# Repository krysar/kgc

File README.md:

# Kerbal Guidance Computer

A HW flight computer for Kerbal Space Program inspired by NASA's DSKY - interface for [Apollo Guidance Computer](https://en.wikipedia.org/wiki/Apollo_Guidance_Computer).

It consists of Python script for PC which grab data from the [kRPC mod](https://krpc.github.io/krpc/index.html), KGC's DSKY based on Raspberry Pi Pico and program for it. DSKY communicate with PC via UART, so you also need some USB-UART converter. KiCad project for DSKY is located in kicad directory.

**Project is still in developement, it's pretty buggy and some of planned features are stil unimplemented.**

## Features
### Implemented
- Display several flight informations depending on selected Verb and Noun.
- Ship control:
    - SAS control
    - RCS control
    - Gear control
    - Lights control
    - Brakes control
    - Solar panels control (extend/retract)
    - Antennas control (extend/retract)
    - Next stage activation
    - Abort group activation
- Maneuver planning
- MechJeb control:
    - Ascent guidance
### Planned
- Ship control:
    - Thrust control
- MechJeb control:
    - Landing guidance
    - Rendezvous autopilot
    - Docking autopilot
    - Maneuver planner

## Installation
TODO

## Usage
TODO

## Verbs and Nouns list

| Verb | Noun | Input/Output                                 | Actions                               | Notes                                                                |
|------|------|----------------------------------------------|---------------------------------------|----------------------------------------------------------------------|
| 00   | 00   |                                              | No op                                 |                                                                      |
| 01   | 01   |                                              | Disconnect from server                |                                                                      |
| 00   | 02   |                                              | Reboot                                |                                                                      |
| 01   | 00   |                                              | No op                                 |                                                                      |
| 01   | 01   | O: Altitude above sea level [m]              |                                       |                                                                      |
|      |      | O: Apoapsis [m]                              |                                       |                                                                      |
|      |      | O: Periapsis [m]                             |                                       |                                                                      |
| 01   | 02   | O: Orbital inclination [°]                   |                                       |                                                                      |
|      |      | O: Orbital eccentricity [°]                  |                                       |                                                                      |
|      |      | O: Mean anomaly [°]                          |                                       |                                                                      |
| 01   | 03   | O: Time to apoapsis [hrs]                    |                                       |                                                                      |
|      |      | O: Time to apoapsis [min]                    |                                       |                                                                      |
|      |      | O: Time to apoapsis [sec]                    |                                       |                                                                      |
| 01   | 04   | O: Time to apoapsis [days]                   |                                       |                                                                      |
|      |      | O: Time to apoapsis [hrs]                    |                                       |                                                                      |
|      |      | O: Time to apoapsis [min]                    |                                       | Kerbin days                                                          |
| 01   | 05   | O: Time to periapsis [hrs]                   |                                       |                                                                      |
|      |      | O: Time to periapsis [min]                   |                                       |                                                                      |
|      |      | O: Time to periapsis [sec]                   |                                       |                                                                      |
| 01   | 06   | O: Time to periapsis [days]                  |                                       |                                                                      |
|      |      | O: Time to periapsis [hrs]                   |                                       |                                                                      |
|      |      | O: Time to periapsis [min]                   |                                       | Kerbin days                                                          |
| 01   | 07   | O: Orbital period [hrs]                      |                                       |                                                                      |
|      |      | O: Orbital period [min]                      |                                       |                                                                      |
|      |      | O: Orbital period [sec]                      |                                       |                                                                      |
| 01   | 08   | O: Orbital period [days]                     |                                       |                                                                      |
|      |      | O: Orbital period [hrs]                      |                                       |                                                                      |
|      |      | O: Orbital period [min]                      |                                       | Kerbin days                                                          |
| 01   | 09   | O: Time to sphere of influence change [hrs]  |                                       |                                                                      |
|      |      | O: Time to sphere of influence change [min]  |                                       |                                                                      |
|      |      | O: Time to sphere of influence change [sec]  |                                       |                                                                      |
| 01   | 10   | O: Time to sphere of influence change [days] |                                       |                                                                      |
|      |      | O: Time to sphere of influence change [hrs]  |                                       |                                                                      |
|      |      | O: Time to sphere of influence change [min]  |                                       | Kerbin days                                                          |
| 01   | 11   | O: Heading [°]                               |                                       | TODO: check ref. frame                                               |
|      |      | O: Pitch [°]                                 |                                       | TODO: check ref. frame                                               |
|      |      | O: Roll [°]                                  |                                       | TODO: check ref. frame                                               |
| 01   | 12   | O: Velocity - x [m/s]                        |                                       | TODO: check ref. frame                                               |
|      |      | O: Velocity - y [m/s]                        |                                       |                                                                      |
|      |      | O: Velocity - z [m/s]                        |                                       |                                                                      |
| 01   | 13   | O: Orbital speed [m/s]                       |                                       |                                                                      |
|      |      | O: Surface speed [m/s]                       |                                       |                                                                      |
| 02   | 00   |                                              | No op                                 |                                                                      |
| 02   | 01   | O: Mission elapsed time [hrs]                |                                       |                                                                      |
|      |      | O: Mission elapsed time [min]                |                                       |                                                                      |
|      |      | O: Mission elapsed time [sec]                |                                       | Strange bug                                                          |
| 02   | 02   | O: Mission elapsed time [days]               |                                       |                                                                      |
|      |      | O: Mission elapsed time [min]                |                                       | Strange bug                                                          |
|      |      | O: Mission elapsed time [hrs]                |                                       | Strange bug                                                          |
| 02   | 03   | O: Mass [kg]                                 |                                       |                                                                      |
|      |      | O: Available thurst [N]                      |                                       |                                                                      |
|      |      | O: Specific impulse [sec]                    |                                       |                                                                      |
| 02   | 04   | O: Electric charge capacity [-]              |                                       |                                                                      |
|      |      | O: Monopropellant capacity [-]               |                                       |                                                                      |
|      |      | O: Liquid fuel capacity [-]                  |                                       |                                                                      |
| 02   | 05   | O: Electric charge amount [-]                |                                       | TODO: float                                                          |
|      |      | O: Monopropellant amount [-]                 |                                       | TODO: float                                                          |
|      |      | O: Liquid fuel amount [-]                    |                                       | TODO: float                                                          |
| 02   | 06   | O: Electric charge amount [%]                |                                       |                                                                      |
|      |      | O: Monopropellant amount [%]                 |                                       |                                                                      |
|      |      | O: Liquid fuel amount [%]                    |                                       |                                                                      |
| 02   | 07   | O: Electric charge capacity [-]              |                                       |                                                                      |
|      |      | O: Electric charge amount [-]                |                                       | TODO: float                                                          |
|      |      | O: Electric charge amount [%]                |                                       |                                                                      |
| 02   | 08   | O: Monopropellant capacity [-]               |                                       |                                                                      |
|      |      | O: Monopropellant amount [-]                 |                                       | TODO: float                                                          |
|      |      | O: Monopropellant amount [%]                 |                                       |                                                                      |
| 02   | 09   | O: Liquid fuel capacity [-]                  |                                       |                                                                      |
|      |      | O: Liquid fuel amount [-]                    |                                       | TODO: float                                                          |
|      |      | O: Liquid fuel amount [%]                    |                                       |                                                                      |
| 03   | 01   | O: Surface speed [m/s]                       |                                       |                                                                      |
|      |      | O: Vertical speed [m/s]                      |                                       |                                                                      |
|      |      | O: Altitude above surface [m]                |                                       |                                                                      |
| 03   | 02   | O: Altitude above sea level                  |                                       |                                                                      |
|      |      | O: Apoapsis [m]                              |                                       |                                                                      |
|      |      | O: Orbital inclination [°]                   |                                       |                                                                      |
| 03   | 03   | O: Apoapsis [m]                              |                                       |                                                                      |
|      |      | O: Periapsis [m]                             |                                       |                                                                      |
|      |      | O: Orbital inclination [°]                   |                                       |                                                                      |
| 04   | 01   | O: Time to node [hrs]                        |                                       |                                                                      |
|      |      | O: Time to node [min]                        |                                       |                                                                      |
|      |      | O: Time to node [sec]                        |                                       |                                                                      |
| 04   | 02   | O: Δv magnitude - prograde direction [m/s]   |                                       |                                                                      |
|      |      | O: Δv magnitude - normal direction [m/s]     |                                       |                                                                      |
|      |      | O: Δv magnitude - radial direction [m/s]     |                                       |                                                                      |
| 04   | 03   | O: Δv [m/s]                                  |                                       |                                                                      |
|      |      | O: Remaining Δv [m/s]                        |                                       |                                                                      |
|      |      | O: Time to node [sec]                        |                                       |                                                                      |
| 04   | 04   | O: Result apoapsis [m]                       |                                       |                                                                      |
|      |      | O: Result periapsis [m]                      |                                       |                                                                      |
|      |      | O: Result inclination [°]                    |                                       |                                                                      |
| 05   | 01   | O: Altitude above surface [m]                |                                       |                                                                      |
|      |      | O: Surface speed [m/s]                       |                                       |                                                                      |
|      |      | O: Liquid fuel amount [%]                    |                                       |                                                                      |
| 05   | 02   | O: Altitude above surface [m]                |                                       |                                                                      |
|      |      | O: Vertical speed [m/s]                      |                                       |                                                                      |
|      |      | O: Horizontal speed [m/s]                    |                                       |                                                                      |
| 12   | 01   |                                              | Activate SAS in stability assist mode | Then return to previous Verb + Noun                                  |
| 12   | 02   |                                              | Activate SAS in maneuver mode         | Then return to previous Verb + Noun                                  |
| 12   | 03   |                                              | Activate SAS in prograde mode         | Then return to previous Verb + Noun                                  |
| 12   | 04   |                                              | Activate SAS in retrograde mode       | Then return to previous Verb + Noun                                  |
| 12   | 05   |                                              | Activate SAS in normal mode           | Then return to previous Verb + Noun                                  |
| 12   | 06   |                                              | Activate SAS in anti-normal mode      | Then return to previous Verb + Noun                                  |
| 12   | 07   |                                              | Activate SAS in radial mode           | Then return to previous Verb + Noun                                  |
| 12   | 08   |                                              | Activate SAS in anti-radial mode      | Then return to previous Verb + Noun                                  |
| 12   | 09   |                                              | Activate SAS in target mode           | Then return to previous Verb + Noun                                  |
| 12   | 10   |                                              | Activate SAS in anti-targer mode      | Then return to previous Verb + Noun                                  |
| 12   | 11   |                                              | Deactivate SAS                        | Then return to previous Verb + Noun                                  |
| 12   | 12   |                                              | Activate RCS                          | Then return to previous Verb + Noun                                  |
| 12   | 13   |                                              | Deactivate RCS                        | Then return to previous Verb + Noun                                  |
| 12   | 14   |                                              | Extend gear                           | Then return to previous Verb + Noun                                  |
| 12   | 15   |                                              | Retract gear                          | Then return to previous Verb + Noun                                  |
| 12   | 16   |                                              | Activate ligts                        | Then return to previous Verb + Noun                                  |
| 12   | 17   |                                              | Deactivate lights                     | Then return to previous Verb + Noun                                  |
| 12   | 18   |                                              | Activate brakes                       | Then return to previous Verb + Noun                                  |
| 12   | 19   |                                              | Deactivate brakes                     | Then return to previous Verb + Noun                                  |
| 12   | 20   |                                              | Extend solar panels                   | Then return to previous Verb + Noun                                  |
| 12   | 21   |                                              | Retract solar panels                  | Then return to previous Verb + Noun                                  |
| 12   | 22   |                                              | Extend antennas                       | Then return to previous Verb + Noun                                  |
| 12   | 23   |                                              | Retract antennas                      | Then return to previous Verb + Noun                                  |
| 12   | 24   |                                              | Activate next stage                   | Then return to previous Verb + Noun                                  |
| 12   | 25   |                                              | Activate abort group                  | Then return to previous Verb + Noun                                  |
| 12   | 30   |                                              | Initialize node creation              |                                                                      |
| 12   | 31   | I: UT - year                                 |                                       |                                                                      |
|      |      | I: UT - day                                  |                                       |                                                                      |
| 12   | 32   | O: UT - year                                 |                                       |                                                                      |
|      |      | O: UT - day                                  |                                       |                                                                      |
| 12   | 33   | I: UT - hour                                 |                                       |                                                                      |
|      |      | I: UT - minute                               |                                       |                                                                      |
|      |      | I: UT - second                               |                                       |                                                                      |
| 12   | 34   | O: UT - hour                                 |                                       |                                                                      |
|      |      | O: UT - minute                               |                                       |                                                                      |
|      |      | O: UT - second                               |                                       |                                                                      |
| 12   | 35   | I: Δv - prograde [m/s]                       |                                       |                                                                      |
|      |      | I: Δv - normal [m/s]                         |                                       |                                                                      |
|      |      | I: Δv - radial [m/s]                         |                                       |                                                                      |
| 12   | 36   | O: Δv - prograde [m/s]                       |                                       |                                                                      |
|      |      | O: Δv - normal [m/s]                         |                                       |                                                                      |
|      |      | O: Δv - radial [m/s]                         |                                       |                                                                      |
| 12   | 37   |                                              | Create node                           | Incorrect time                                                       |
| 13   | 00   |                                              | Initialize ascent autpoilot           | MechJeb is used                                                      |
| 13   | 01   | I: Orbit altitude [km]                       |                                       |                                                                      |
|      |      | I: Orbit inclination [°]                     |                                       |                                                                      |
|      |      | I: Ascent profile {1; 2; 3}                  |                                       | 1 = Classic ascent profile                                           |
|      |      |                                              |                                       | 2 = Stock-style GravityTurn ascent profile                           |
|      |      |                                              |                                       | 3 = Primer Vector Guidance ascent profile                            |
| 13   | 02   | O: Orbit altitude [km]                       |                                       |                                                                      |
|      |      | O: Orbit inclination [°]                     |                                       |                                                                      |
|      |      | O: Ascent profile {1; 2; 3}                  |                                       |                                                                      |
| 13   | 03   | I: Acceleration limit [m/s]                  |                                       | -1 for disable; -2 for ignore                                        |
|      |      | I: Throttle limit [%]                        |                                       | -1 for disable; -2 for ignore                                        |
| 13   | 04   | O: Acceleration limit [m/s]                  |                                       |                                                                      |
|      |      | O: Throttle limit [%]                        |                                       |                                                                      |
| 13   | 05   | I: Force roll - climb [°]                    |                                       | -1 for disable; -2 for ignore (whole force roll)                     |
|      |      | I: Force roll - turn [°]                     |                                       |                                                                      |
| 13   | 06   | O: Force roll - climb [°]                    |                                       |                                                                      |
|      |      | O: Force roll - turn [°]                     |                                       |                                                                      |
| 13   | 07   | I: Autostage pre-delay [s]                   |                                       | -1 for disable; -2 for ignore (whole autostage)                      |
|      |      | I: Autostage post-delay [s]                  |                                       |                                                                      |
|      |      | I: Clamp autostage thrust [%]                |                                       |                                                                      |
| 13   | 08   | O: Autostage pre-delay [s]                   |                                       |                                                                      |
|      |      | O: Autostage post-delay [s]                  |                                       |                                                                      |
|      |      | O: Clamp autostage thrust [%]                |                                       |                                                                      |
| 13   | 09   | I: Minimal throttle [%]                      |                                       | -1 for disable; -2 for ignore                                        |
|      |      | I: Autostage stop stage                      |                                       | Details in truth table                                               |
|      |      | I: Other options                             |                                       |                                                                      |
| 13   | 10   | O: Minimal throttle [%]                      |                                       |                                                                      |
|      |      | O: Autostage stop stage                      |                                       |                                                                      |
|      |      | O: Other options                             |                                       |                                                                      |
| 13   | 11   | I: Turn start altitude [km]                  |                                       | Classic ascent profile                                               |
|      |      | I: Turn start velocity [m/s]                 |                                       | Classic ascent profile                                               |
|      |      | I: Turn end altitude [km]                    |                                       | Classic ascent profile                                               |
| 13   | 12   | O: Turn start altitude [km]                  |                                       | Classic ascent profile                                               |
|      |      | O: Turn start velocity [m/s]                 |                                       | Classic ascent profile                                               |
|      |      | O: Turn end altitude [km]                    |                                       | Classic ascent profile                                               |
| 13   | 13   | I: Final flight path angle [°]               |                                       | Classic ascent profile; -1 for disable; -2 for ignore                |
|      |      | I: Turn shape [%]                            |                                       | Classic ascent profile; -1 for disable; -2 for ignore                |
| 13   | 14   | O: Final flight path angle [°]               |                                       | Classic ascent profile                                               |
|      |      | O: Turn shape [%]                            |                                       | Classic ascent profile                                               |
| 13   | 15   | I: Turn start altitude [km]                  |                                       | Stock-style GravityTurn ascent profile                               |
|      |      | I: Turn start velocity [m/s]                 |                                       | Stock-style GravityTurn ascent profile                               |
|      |      | I: Turn start pitch [°]                      |                                       | Stock-style GravityTurn ascent profile                               |
| 13   | 16   | O: Turn start altitude [km]                  |                                       | Stock-style GravityTurn ascent profile                               |
|      |      | O: Turn start velocity [m/s]                 |                                       | Stock-style GravityTurn ascent profile                               |
|      |      | O: Turn start pitch [°]                      |                                       | Stock-style GravityTurn ascent profile                               |
| 13   | 17   | I: Intermediate altitude [km]                |                                       | Stock-style GravityTurn ascent profile                               |
|      |      | I: Hold AP time [s]                          |                                       | Stock-style GravityTurn ascent profile                               |
| 13   | 18   | O: Intermediate altitude [km]                |                                       | Stock-style GravityTurn ascent profile                               |
|      |      | O: Hold AP time [s]                          |                                       | Stock-style GravityTurn ascent profile                               |
| 13   | 19   | I: Apoapsis altitude [km]                    |                                       | Primer Vector Guidance ascent profile                                |
|      |      | I: Attach altitude [km]                      |                                       | Primer Vector Guidance ascent profile                                |
|      |      | I: Booster pitch start velocity [m/s]        |                                       | Primer Vector Guidance ascent profile                                |
| 13   | 20   | O: Apoapsis altitude [km]                    |                                       | Primer Vector Guidance ascent profile                                |
|      |      | O: Attach altitude [km]                      |                                       | Primer Vector Guidance ascent profile                                |
|      |      | O: Booster pitch start velocity [m/s]        |                                       | Primer Vector Guidance ascent profile                                |
| 13   | 21   | I: Booster pitch rate [°/s]                  |                                       | Primer Vector Guidance ascent profile                                |
|      |      | I: PVG after stage                           |                                       | Primer Vector Guidance ascent profile; -1 for disable; -2 for ignore |
| 13   | 22   | O: Booster pitch rate [°/s]                  |                                       | Primer Vector Guidance ascent profile                                |
|      |      | O: PVG after stage                           |                                       | Primer Vector Guidance ascent profile                                |
| 13   | 23   | I: Q trigger [kPa]                           |                                       | Primer Vector Guidance ascent profile                                |
|      |      | I: Fixed coast length [s]                    |                                       | Primer Vector Guidance ascent profile; -1 for disable; -2 for ignore |
| 13   | 24   | O: Q trigger [kPa]                           |                                       | Primer Vector Guidance ascent profile                                |
|      |      | O: Fixed coast length [s]                    |                                       | Primer Vector Guidance ascent profile                                |
| 13   | 25   |                                              | Enage ascent autopilot                |                                                                      |
| 13   | 26   |                                              | Disenage ascent autopilot             |                                                                      |

## Truth table for other options value in Ascent autopilot

| Prevent overheat | Solar panels | Antennas | Skip circularization | Dec |
|------------------|--------------|----------|----------------------|-----|
| 0                | 0            | 0        | 0                    | 0   |
| 0                | 0            | 0        | 1                    | 1   |
| 0                | 0            | 1        | 0                    | 2   |
| 0                | 0            | 1        | 1                    | 3   |
| 0                | 1            | 0        | 0                    | 4   |
| 0                | 1            | 0        | 1                    | 5   |
| 0                | 1            | 1        | 0                    | 6   |
| 0                | 1            | 1        | 1                    | 7   |
| 1                | 0            | 0        | 0                    | 8   |
| 1                | 0            | 0        | 1                    | 9   |
| 1                | 0            | 1        | 0                    | 10  |
| 1                | 0            | 1        | 1                    | 11  |
| 1                | 1            | 0        | 0                    | 12  |
| 1                | 1            | 0        | 1                    | 13  |
| 1                | 1            | 1        | 0                    | 14  |
| 1                | 1            | 1        | 1                    | 15  |

## Error codes
### Ascent guidance:
- 1301: Noun doesn't exist
- 1302: Autopilot wasn't initialized
- 1303: Ascent profile selected in V13;N01 doesn't exist

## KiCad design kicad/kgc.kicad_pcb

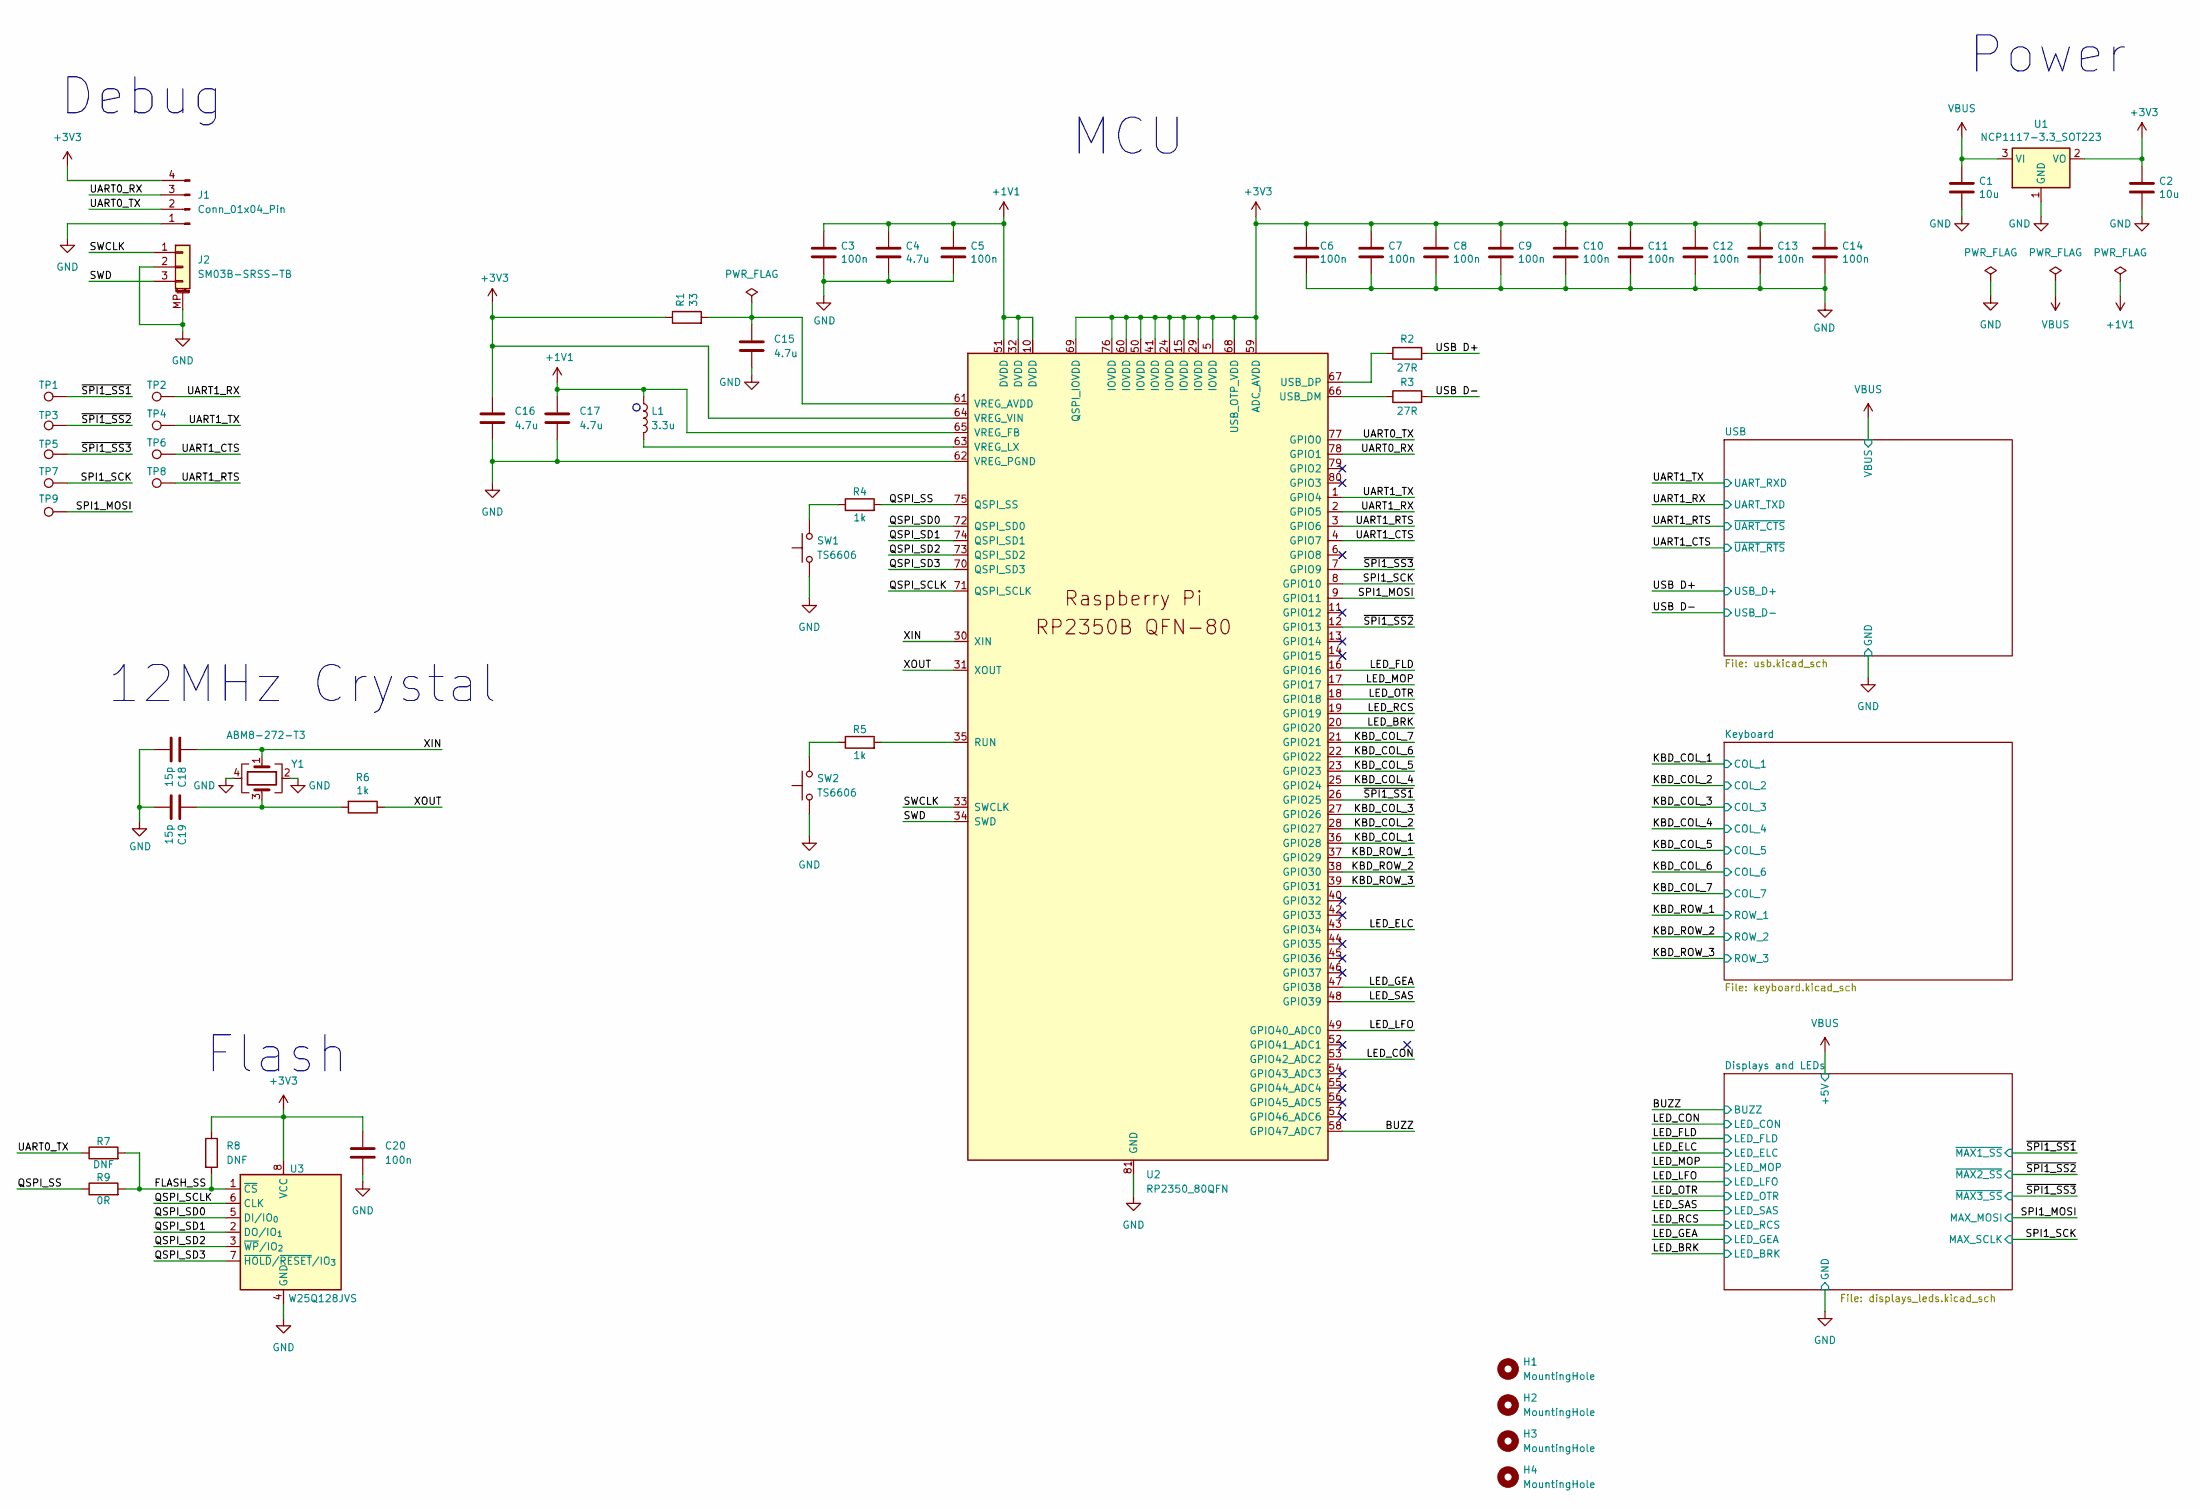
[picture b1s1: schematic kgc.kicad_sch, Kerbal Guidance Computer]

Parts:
C1, C2: 10u; C_0603_1608Metric_Pad1.08x0.95mm_HandSolder
C3, C5, C6, C7, C8, C9, C10, C11, C12, C13, C14, C20: 100n; C_0603_1608Metric_Pad1.08x0.95mm_HandSolder
C4, C15, C16, C17: 4.7u; C_0603_1608Metric_Pad1.08x0.95mm_HandSolder
C18, C19: 15p; C_0603_1608Metric_Pad1.08x0.95mm_HandSolder
H1, H2, H3, H4: MountingHole; MountingHole_3.2mm_M3
J1: Conn_01x04_Pin; PinHeader_1x04_P2.54mm_Horizontal
J2: SM03B-SRSS-TB; JST_SH_SM03B-SRSS-TB_1x03-1MP_P1.00mm_Horizontal
L1: 3.3u; L_pol_2016
R1: 33; R_0603_1608Metric_Pad0.98x0.95mm_HandSolder
R2, R3: 27R; R_0603_1608Metric_Pad0.98x0.95mm_HandSolder
R4, R5, R6: 1k; R_0603_1608Metric_Pad0.98x0.95mm_HandSolder
R7, R8: DNF; R_0603_1608Metric_Pad0.98x0.95mm_HandSolder
R9: 0R; R_0603_1608Metric_Pad0.98x0.95mm_HandSolder
SW1, SW2: TS6606; SW_Tactile_SKHH_Angled
TP1, TP2, TP3, TP4, TP5, TP6, TP7, TP8, TP9: TestPoint; TestPoint_Plated_Hole_D2.0mm
U1: NCP1117-3.3_SOT223; SOT-223-3_TabPin2; LCSC C26537
U2: RP2350_80QFN; RP2350-QFN-80-1EP_10x10_P0.4mm_EP3.4x3.4mm_ThermalVias; LCSC C42415655
U3: W25Q128JVS; SOIC-8_5.3x5.3mm_P1.27mm; LCSC C97521
Y1: ABM8-272-T3; Crystal_SMD_3225-4Pin_3.2x2.5mm; LCSC C20625731

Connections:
+1V1: C3.1, C4.1, C5.1, C17.1, L1.1, U2.10 (DVDD), U2.32 (DVDD), U2.51 (DVDD), U2.65 (VREG_FB)
+3V3: C2.1, C6.1, C7.1, C8.1, C9.1, C10.1, C11.1, C12.1, C13.1, C14.1, C16.1, C20.1, J1.4, R1.1, R8.1, U1.2 (VO), U2.5 (IOVDD), U2.15 (IOVDD), U2.24 (IOVDD), U2.29 (IOVDD), U2.41 (IOVDD), U2.50 (IOVDD), U2.59 (ADC_AVDD), U2.60 (IOVDD), U2.64 (VREG_VIN), U2.68 (USB_OTP_VDD), U2.69 (QSPI_IOVDD), U2.76 (IOVDD), U3.8 (VCC)
/BUZZ: U2.58 (GPIO47_ADC7); also elsewhere on the board
/FLASH_SS: R7.2, R8.2, R9.2, U3.1 (~CS)
/KBD_COL_1: U2.36 (GPIO28); also elsewhere on the board
/KBD_COL_2: U2.28 (GPIO27); also elsewhere on the board
/KBD_COL_3: U2.27 (GPIO26); also elsewhere on the board
/KBD_COL_4: U2.25 (GPIO24); also elsewhere on the board
/KBD_COL_5: U2.23 (GPIO23); also elsewhere on the board
/KBD_COL_6: U2.22 (GPIO22); also elsewhere on the board
/KBD_COL_7: U2.21 (GPIO21); also elsewhere on the board
/KBD_ROW_1: U2.37 (GPIO29); also elsewhere on the board
/KBD_ROW_2: U2.38 (GPIO30); also elsewhere on the board
/KBD_ROW_3: U2.39 (GPIO31); also elsewhere on the board
/LED_BRK: U2.20 (GPIO20); also elsewhere on the board
/LED_CON: U2.53 (GPIO42_ADC2); also elsewhere on the board
/LED_ELC: U2.43 (GPIO34); also elsewhere on the board
/LED_FLD: U2.16 (GPIO16); also elsewhere on the board
/LED_GEA: U2.47 (GPIO38); also elsewhere on the board
/LED_LFO: U2.49 (GPIO40_ADC0); also elsewhere on the board
/LED_MOP: U2.17 (GPIO17); also elsewhere on the board
/LED_OTR: U2.18 (GPIO18); also elsewhere on the board
/LED_RCS: U2.19 (GPIO19); also elsewhere on the board
/LED_SAS: U2.48 (GPIO39); also elsewhere on the board
/QSPI_SCLK: U2.71 (QSPI_SCLK), U3.6 (CLK)
/QSPI_SD0: U2.72 (QSPI_SD0), U3.5 (DI/IO_{0})
/QSPI_SD1: U2.74 (QSPI_SD1), U3.2 (DO/IO_{1})
/QSPI_SD2: U2.73 (QSPI_SD2), U3.3 (~WP/IO_{2})
/QSPI_SD3: U2.70 (QSPI_SD3), U3.7 (~HOLD/~RESET/IO_{3})
/QSPI_SS: R4.2, R9.1, U2.75 (QSPI_SS)
/SPI1_MOSI: TP9.1, U2.9 (GPIO11); also elsewhere on the board
/SPI1_SCK: TP7.1, U2.8 (GPIO10); also elsewhere on the board
/SWCLK: J2.1, U2.33 (SWCLK)
/SWD: J2.3, U2.34 (SWD)
/UART0_RX: J1.3, U2.78 (GPIO1)
/UART0_TX: J1.2, R7.1, U2.77 (GPIO0)
/UART1_CTS: TP6.1, U2.4 (GPIO7); also elsewhere on the board
/UART1_RTS: TP8.1, U2.3 (GPIO6); also elsewhere on the board
/UART1_RX: TP2.1, U2.2 (GPIO5); also elsewhere on the board
/UART1_TX: TP4.1, U2.1 (GPIO4); also elsewhere on the board
/USB D+: R2.2; also elsewhere on the board
/USB D-: R3.2; also elsewhere on the board
/XIN: C18.1, U2.30 (XIN), Y1.1
/XOUT: R6.1, U2.31 (XOUT)
/~SPI1_SS1: TP1.1, U2.26 (GPIO25); also elsewhere on the board
/~SPI1_SS2: TP3.1, U2.12 (GPIO13); also elsewhere on the board
/~SPI1_SS3: TP5.1, U2.7 (GPIO9); also elsewhere on the board
GND: C1.2, C2.2, C3.2, C4.2, C5.2, C6.2, C7.2, C8.2, C9.2, C10.2, C11.2, C12.2, C13.2, C14.2, C15.2, C16.2, C17.2, C18.2, C19.2, C20.2, J1.1, J2.2, J2.MP (MountPin), SW1.1, SW2.1, U1.1 (GND), U2.62 (VREG_PGND), U2.81 (GND), U3.4 (GND), Y1.2, Y1.4; also elsewhere on the board
unnamed: C19.1, R6.2, Y1.3
unnamed: R4.1, SW1.2
unnamed: R5.1, SW2.2
unnamed: R5.2, U2.35 (RUN)
unnamed: R3.1, U2.66 (USB_DM)
unnamed: R2.1, U2.67 (USB_DP)
unnamed: C15.1, R1.2, U2.61 (VREG_AVDD)
unnamed: L1.2, U2.63 (VREG_LX)
VBUS: C1.1, U1.3 (VI); also elsewhere on the board

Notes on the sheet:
Debug
12MHz Crystal
Flash
MCU
Power

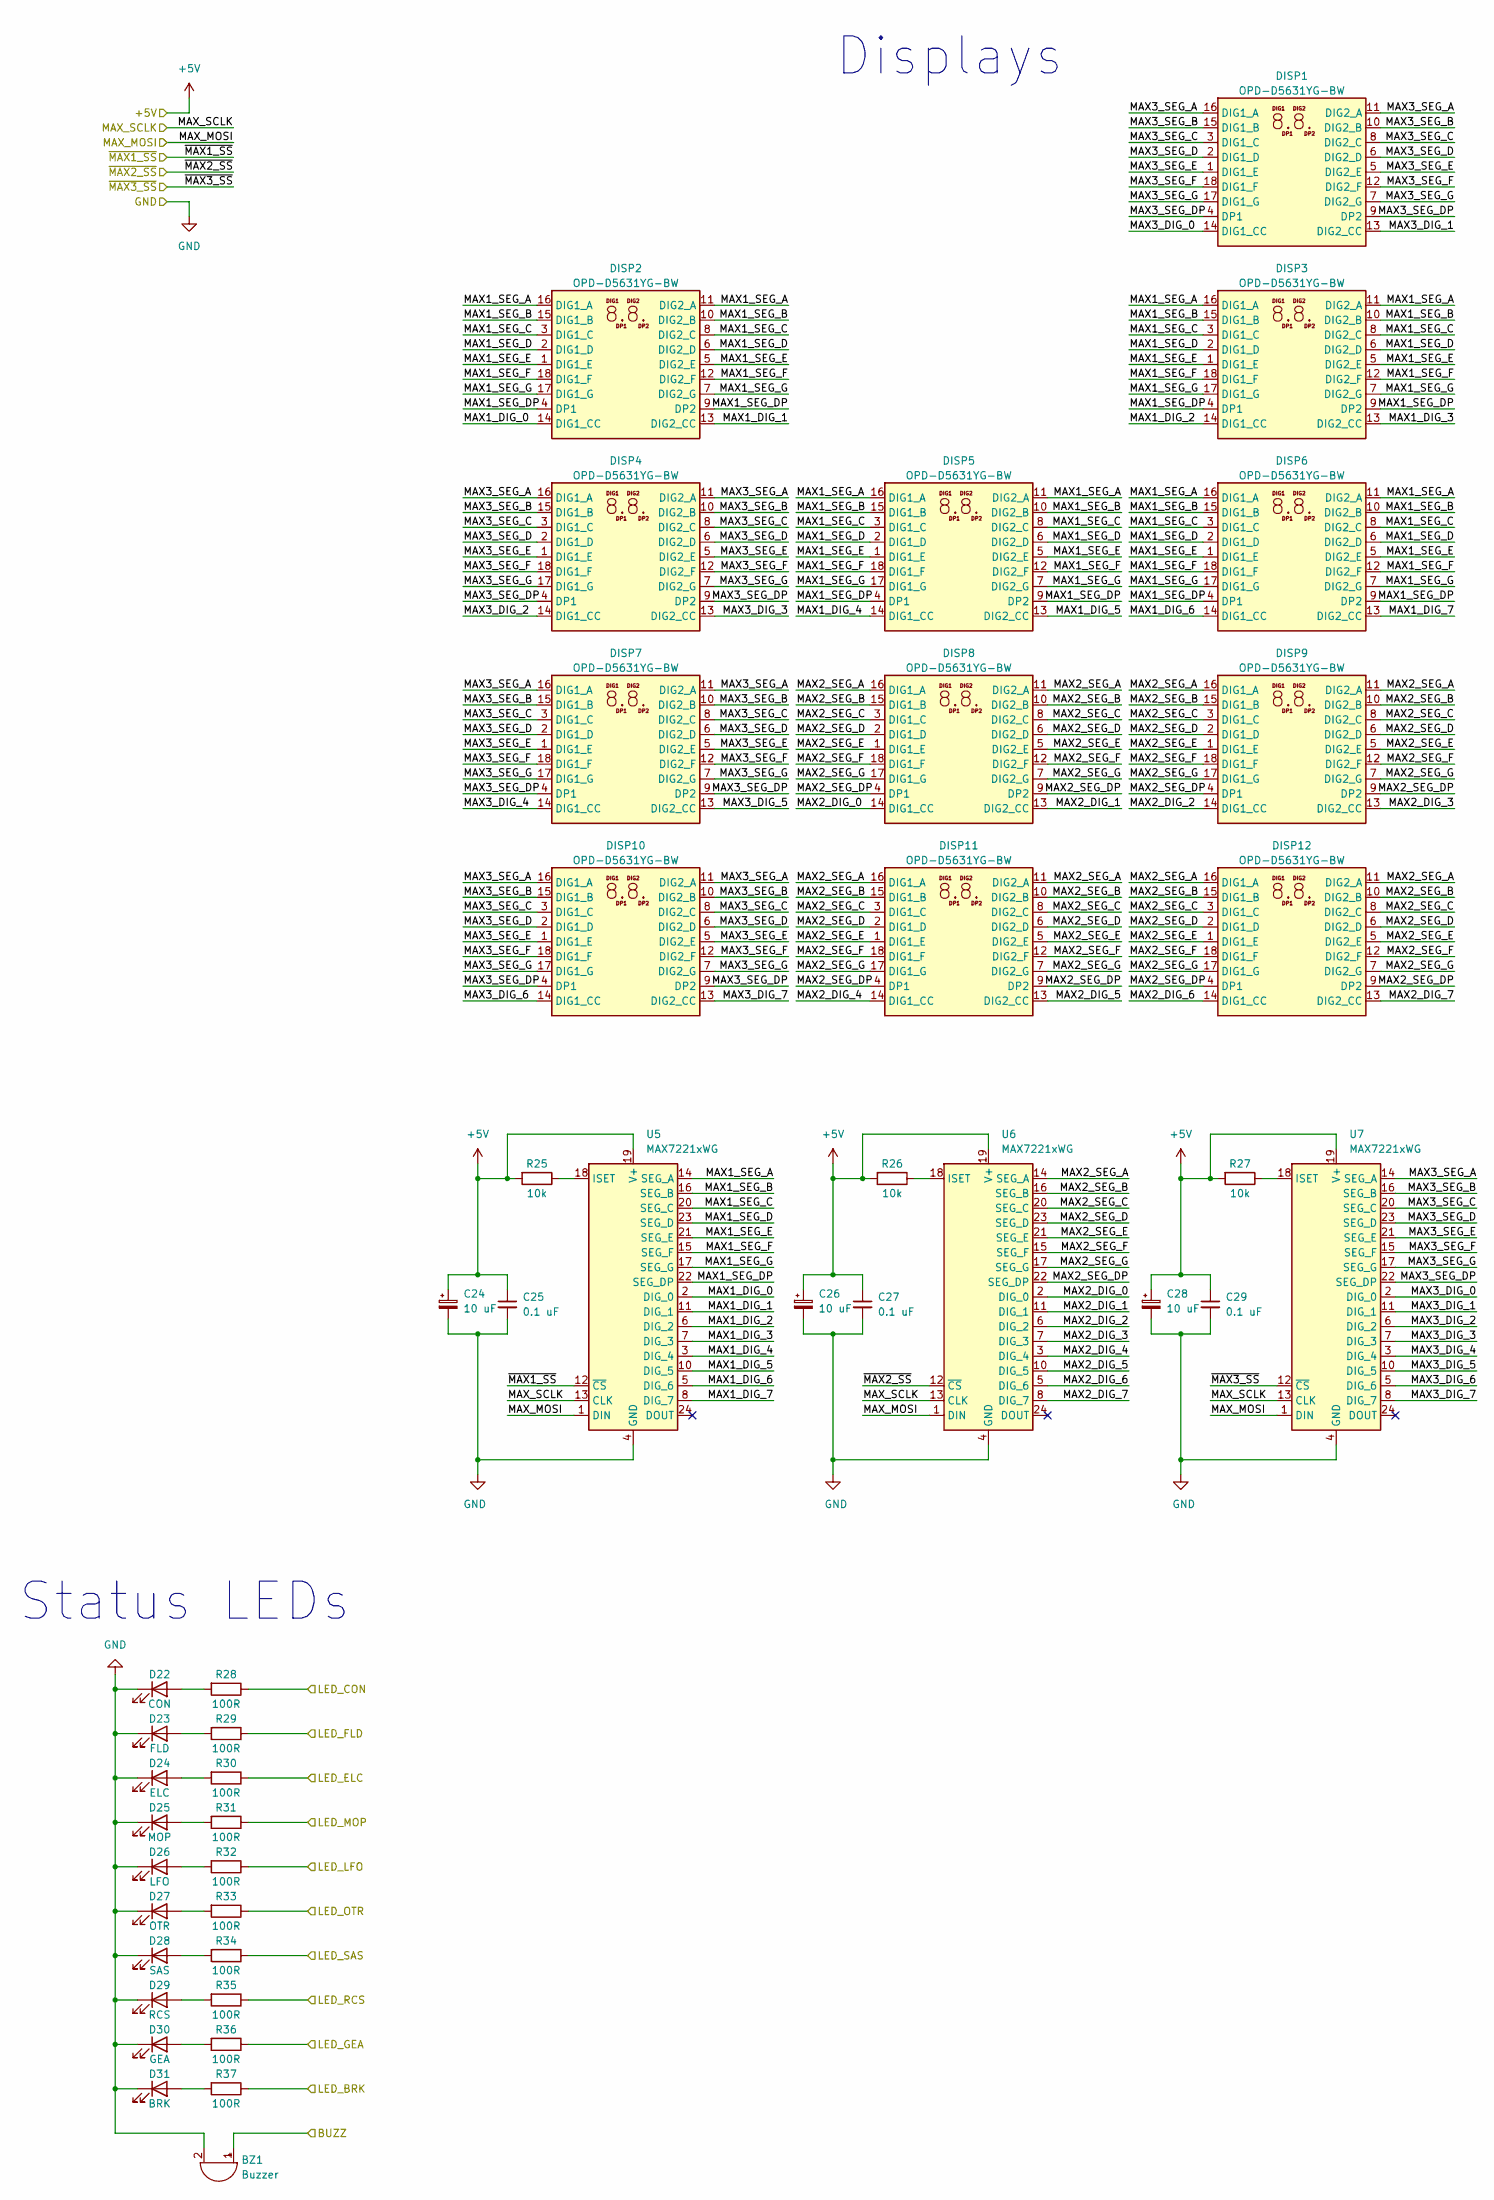
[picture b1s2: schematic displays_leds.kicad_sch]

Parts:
BZ1: Buzzer; Buzzer_XDCR_CPT-1203-03-SMT-TR
C24, C26, C28: 10 uF; CP_Elec_5x4.5
C25, C27, C29: 0.1 uF; C_0603_1608Metric_Pad1.08x0.95mm_HandSolder
D22: CON; LED_0805_2012Metric_Pad1.15x1.40mm_HandSolder
D23: FLD; LED_0805_2012Metric_Pad1.15x1.40mm_HandSolder
D24: ELC; LED_0805_2012Metric_Pad1.15x1.40mm_HandSolder
D25: MOP; LED_0805_2012Metric_Pad1.15x1.40mm_HandSolder
D26: LFO; LED_0805_2012Metric_Pad1.15x1.40mm_HandSolder
D27: OTR; LED_0805_2012Metric_Pad1.15x1.40mm_HandSolder
D28: SAS; LED_0805_2012Metric_Pad1.15x1.40mm_HandSolder
D29: RCS; LED_0805_2012Metric_Pad1.15x1.40mm_HandSolder
D30: GEA; LED_0805_2012Metric_Pad1.15x1.40mm_HandSolder
D31: BRK; LED_0805_2012Metric_Pad1.15x1.40mm_HandSolder
DISP1, DISP2, DISP3, DISP4, DISP5, DISP6, DISP7, DISP8, DISP9, DISP10, DISP11, DISP12: OPD-D5631YG-BW; DA56-11CGKWA
R25, R26, R27: 10k; R_0603_1608Metric_Pad0.98x0.95mm_HandSolder
R28, R29, R30, R31, R32, R33, R34, R35, R36, R37: 100R; R_0603_1608Metric_Pad0.98x0.95mm_HandSolder
U5, U6, U7: MAX7221xWG; SOIC-24W_7.5x15.4mm_P1.27mm; LCSC C155199

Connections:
/BUZZ: BZ1.1 (+); also elsewhere on the board
/Displays and LEDs/MAX1_DIG_0: DISP2.14 (DIG1_CC), U5.2 (DIG_0)
/Displays and LEDs/MAX1_DIG_1: DISP2.13 (DIG2_CC), U5.11 (DIG_1)
/Displays and LEDs/MAX1_DIG_2: DISP3.14 (DIG1_CC), U5.6 (DIG_2)
/Displays and LEDs/MAX1_DIG_3: DISP3.13 (DIG2_CC), U5.7 (DIG_3)
/Displays and LEDs/MAX1_DIG_4: DISP5.14 (DIG1_CC), U5.3 (DIG_4)
/Displays and LEDs/MAX1_DIG_5: DISP5.13 (DIG2_CC), U5.10 (DIG_5)
/Displays and LEDs/MAX1_DIG_6: DISP6.14 (DIG1_CC), U5.5 (DIG_6)
/Displays and LEDs/MAX1_DIG_7: DISP6.13 (DIG2_CC), U5.8 (DIG_7)
/Displays and LEDs/MAX1_SEG_A: DISP2.11 (DIG2_A), DISP2.16 (DIG1_A), DISP3.11 (DIG2_A), DISP3.16 (DIG1_A), DISP5.11 (DIG2_A), DISP5.16 (DIG1_A), DISP6.11 (DIG2_A), DISP6.16 (DIG1_A), U5.14 (SEG_A)
/Displays and LEDs/MAX1_SEG_B: DISP2.10 (DIG2_B), DISP2.15 (DIG1_B), DISP3.10 (DIG2_B), DISP3.15 (DIG1_B), DISP5.10 (DIG2_B), DISP5.15 (DIG1_B), DISP6.10 (DIG2_B), DISP6.15 (DIG1_B), U5.16 (SEG_B)
/Displays and LEDs/MAX1_SEG_C: DISP2.3 (DIG1_C), DISP2.8 (DIG2_C), DISP3.3 (DIG1_C), DISP3.8 (DIG2_C), DISP5.3 (DIG1_C), DISP5.8 (DIG2_C), DISP6.3 (DIG1_C), DISP6.8 (DIG2_C), U5.20 (SEG_C)
/Displays and LEDs/MAX1_SEG_D: DISP2.2 (DIG1_D), DISP2.6 (DIG2_D), DISP3.2 (DIG1_D), DISP3.6 (DIG2_D), DISP5.2 (DIG1_D), DISP5.6 (DIG2_D), DISP6.2 (DIG1_D), DISP6.6 (DIG2_D), U5.23 (SEG_D)
/Displays and LEDs/MAX1_SEG_DP: DISP2.4 (DP1), DISP2.9 (DP2), DISP3.4 (DP1), DISP3.9 (DP2), DISP5.4 (DP1), DISP5.9 (DP2), DISP6.4 (DP1), DISP6.9 (DP2), U5.22 (SEG_DP)
/Displays and LEDs/MAX1_SEG_E: DISP2.1 (DIG1_E), DISP2.5 (DIG2_E), DISP3.1 (DIG1_E), DISP3.5 (DIG2_E), DISP5.1 (DIG1_E), DISP5.5 (DIG2_E), DISP6.1 (DIG1_E), DISP6.5 (DIG2_E), U5.21 (SEG_E)
/Displays and LEDs/MAX1_SEG_F: DISP2.12 (DIG2_F), DISP2.18 (DIG1_F), DISP3.12 (DIG2_F), DISP3.18 (DIG1_F), DISP5.12 (DIG2_F), DISP5.18 (DIG1_F), DISP6.12 (DIG2_F), DISP6.18 (DIG1_F), U5.15 (SEG_F)
/Displays and LEDs/MAX1_SEG_G: DISP2.7 (DIG2_G), DISP2.17 (DIG1_G), DISP3.7 (DIG2_G), DISP3.17 (DIG1_G), DISP5.7 (DIG2_G), DISP5.17 (DIG1_G), DISP6.7 (DIG2_G), DISP6.17 (DIG1_G), U5.17 (SEG_G)
/Displays and LEDs/MAX2_DIG_0: DISP8.14 (DIG1_CC), U6.2 (DIG_0)
/Displays and LEDs/MAX2_DIG_1: DISP8.13 (DIG2_CC), U6.11 (DIG_1)
/Displays and LEDs/MAX2_DIG_2: DISP9.14 (DIG1_CC), U6.6 (DIG_2)
/Displays and LEDs/MAX2_DIG_3: DISP9.13 (DIG2_CC), U6.7 (DIG_3)
/Displays and LEDs/MAX2_DIG_4: DISP11.14 (DIG1_CC), U6.3 (DIG_4)
/Displays and LEDs/MAX2_DIG_5: DISP11.13 (DIG2_CC), U6.10 (DIG_5)
/Displays and LEDs/MAX2_DIG_6: DISP12.14 (DIG1_CC), U6.5 (DIG_6)
/Displays and LEDs/MAX2_DIG_7: DISP12.13 (DIG2_CC), U6.8 (DIG_7)
/Displays and LEDs/MAX2_SEG_A: DISP8.11 (DIG2_A), DISP8.16 (DIG1_A), DISP9.11 (DIG2_A), DISP9.16 (DIG1_A), DISP11.11 (DIG2_A), DISP11.16 (DIG1_A), DISP12.11 (DIG2_A), DISP12.16 (DIG1_A), U6.14 (SEG_A)
/Displays and LEDs/MAX2_SEG_B: DISP8.10 (DIG2_B), DISP8.15 (DIG1_B), DISP9.10 (DIG2_B), DISP9.15 (DIG1_B), DISP11.10 (DIG2_B), DISP11.15 (DIG1_B), DISP12.10 (DIG2_B), DISP12.15 (DIG1_B), U6.16 (SEG_B)
/Displays and LEDs/MAX2_SEG_C: DISP8.3 (DIG1_C), DISP8.8 (DIG2_C), DISP9.3 (DIG1_C), DISP9.8 (DIG2_C), DISP11.3 (DIG1_C), DISP11.8 (DIG2_C), DISP12.3 (DIG1_C), DISP12.8 (DIG2_C), U6.20 (SEG_C)
/Displays and LEDs/MAX2_SEG_D: DISP8.2 (DIG1_D), DISP8.6 (DIG2_D), DISP9.2 (DIG1_D), DISP9.6 (DIG2_D), DISP11.2 (DIG1_D), DISP11.6 (DIG2_D), DISP12.2 (DIG1_D), DISP12.6 (DIG2_D), U6.23 (SEG_D)
/Displays and LEDs/MAX2_SEG_DP: DISP8.4 (DP1), DISP8.9 (DP2), DISP9.4 (DP1), DISP9.9 (DP2), DISP11.4 (DP1), DISP11.9 (DP2), DISP12.4 (DP1), DISP12.9 (DP2), U6.22 (SEG_DP)
/Displays and LEDs/MAX2_SEG_E: DISP8.1 (DIG1_E), DISP8.5 (DIG2_E), DISP9.1 (DIG1_E), DISP9.5 (DIG2_E), DISP11.1 (DIG1_E), DISP11.5 (DIG2_E), DISP12.1 (DIG1_E), DISP12.5 (DIG2_E), U6.21 (SEG_E)
/Displays and LEDs/MAX2_SEG_F: DISP8.12 (DIG2_F), DISP8.18 (DIG1_F), DISP9.12 (DIG2_F), DISP9.18 (DIG1_F), DISP11.12 (DIG2_F), DISP11.18 (DIG1_F), DISP12.12 (DIG2_F), DISP12.18 (DIG1_F), U6.15 (SEG_F)
/Displays and LEDs/MAX2_SEG_G: DISP8.7 (DIG2_G), DISP8.17 (DIG1_G), DISP9.7 (DIG2_G), DISP9.17 (DIG1_G), DISP11.7 (DIG2_G), DISP11.17 (DIG1_G), DISP12.7 (DIG2_G), DISP12.17 (DIG1_G), U6.17 (SEG_G)
/Displays and LEDs/MAX3_DIG_0: DISP1.14 (DIG1_CC), U7.2 (DIG_0)
/Displays and LEDs/MAX3_DIG_1: DISP1.13 (DIG2_CC), U7.11 (DIG_1)
/Displays and LEDs/MAX3_DIG_2: DISP4.14 (DIG1_CC), U7.6 (DIG_2)
/Displays and LEDs/MAX3_DIG_3: DISP4.13 (DIG2_CC), U7.7 (DIG_3)
/Displays and LEDs/MAX3_DIG_4: DISP7.14 (DIG1_CC), U7.3 (DIG_4)
/Displays and LEDs/MAX3_DIG_5: DISP7.13 (DIG2_CC), U7.10 (DIG_5)
/Displays and LEDs/MAX3_DIG_6: DISP10.14 (DIG1_CC), U7.5 (DIG_6)
/Displays and LEDs/MAX3_DIG_7: DISP10.13 (DIG2_CC), U7.8 (DIG_7)
/Displays and LEDs/MAX3_SEG_A: DISP1.11 (DIG2_A), DISP1.16 (DIG1_A), DISP4.11 (DIG2_A), DISP4.16 (DIG1_A), DISP7.11 (DIG2_A), DISP7.16 (DIG1_A), DISP10.11 (DIG2_A), DISP10.16 (DIG1_A), U7.14 (SEG_A)
/Displays and LEDs/MAX3_SEG_B: DISP1.10 (DIG2_B), DISP1.15 (DIG1_B), DISP4.10 (DIG2_B), DISP4.15 (DIG1_B), DISP7.10 (DIG2_B), DISP7.15 (DIG1_B), DISP10.10 (DIG2_B), DISP10.15 (DIG1_B), U7.16 (SEG_B)
/Displays and LEDs/MAX3_SEG_C: DISP1.3 (DIG1_C), DISP1.8 (DIG2_C), DISP4.3 (DIG1_C), DISP4.8 (DIG2_C), DISP7.3 (DIG1_C), DISP7.8 (DIG2_C), DISP10.3 (DIG1_C), DISP10.8 (DIG2_C), U7.20 (SEG_C)
/Displays and LEDs/MAX3_SEG_D: DISP1.2 (DIG1_D), DISP1.6 (DIG2_D), DISP4.2 (DIG1_D), DISP4.6 (DIG2_D), DISP7.2 (DIG1_D), DISP7.6 (DIG2_D), DISP10.2 (DIG1_D), DISP10.6 (DIG2_D), U7.23 (SEG_D)
/Displays and LEDs/MAX3_SEG_DP: DISP1.4 (DP1), DISP1.9 (DP2), DISP4.4 (DP1), DISP4.9 (DP2), DISP7.4 (DP1), DISP7.9 (DP2), DISP10.4 (DP1), DISP10.9 (DP2), U7.22 (SEG_DP)
/Displays and LEDs/MAX3_SEG_E: DISP1.1 (DIG1_E), DISP1.5 (DIG2_E), DISP4.1 (DIG1_E), DISP4.5 (DIG2_E), DISP7.1 (DIG1_E), DISP7.5 (DIG2_E), DISP10.1 (DIG1_E), DISP10.5 (DIG2_E), U7.21 (SEG_E)
/Displays and LEDs/MAX3_SEG_F: DISP1.12 (DIG2_F), DISP1.18 (DIG1_F), DISP4.12 (DIG2_F), DISP4.18 (DIG1_F), DISP7.12 (DIG2_F), DISP7.18 (DIG1_F), DISP10.12 (DIG2_F), DISP10.18 (DIG1_F), U7.15 (SEG_F)
/Displays and LEDs/MAX3_SEG_G: DISP1.7 (DIG2_G), DISP1.17 (DIG1_G), DISP4.7 (DIG2_G), DISP4.17 (DIG1_G), DISP7.7 (DIG2_G), DISP7.17 (DIG1_G), DISP10.7 (DIG2_G), DISP10.17 (DIG1_G), U7.17 (SEG_G)
/LED_BRK: R37.1; also elsewhere on the board
/LED_CON: R28.1; also elsewhere on the board
/LED_ELC: R30.1; also elsewhere on the board
/LED_FLD: R29.1; also elsewhere on the board
/LED_GEA: R36.1; also elsewhere on the board
/LED_LFO: R32.1; also elsewhere on the board
/LED_MOP: R31.1; also elsewhere on the board
/LED_OTR: R33.1; also elsewhere on the board
/LED_RCS: R35.1; also elsewhere on the board
/LED_SAS: R34.1; also elsewhere on the board
/SPI1_MOSI: U5.1 (DIN), U6.1 (DIN), U7.1 (DIN); also elsewhere on the board
/SPI1_SCK: U5.13 (CLK), U6.13 (CLK), U7.13 (CLK); also elsewhere on the board
/~SPI1_SS1: U5.12 (~CS); also elsewhere on the board
/~SPI1_SS2: U6.12 (~CS); also elsewhere on the board
/~SPI1_SS3: U7.12 (~CS); also elsewhere on the board
GND: BZ1.2 (-), C24.2, C25.2, C26.2, C27.2, C28.2, C29.2, D22.1 (K), D23.1 (K), D24.1 (K), D25.1 (K), D26.1 (K), D27.1 (K), D28.1 (K), D29.1 (K), D30.1 (K), D31.1 (K), U5.4 (GND), U5.9 (GND), U6.4 (GND), U6.9 (GND), U7.4 (GND), U7.9 (GND); also elsewhere on the board
unnamed: D22.2 (A), R28.2
unnamed: D23.2 (A), R29.2
unnamed: D24.2 (A), R30.2
unnamed: D25.2 (A), R31.2
unnamed: D26.2 (A), R32.2
unnamed: D27.2 (A), R33.2
unnamed: D28.2 (A), R34.2
unnamed: D29.2 (A), R35.2
unnamed: D30.2 (A), R36.2
unnamed: D31.2 (A), R37.2
unnamed: R25.1, U5.18 (ISET)
unnamed: R26.1, U6.18 (ISET)
unnamed: R27.1, U7.18 (ISET)
VBUS: C24.1, C25.1, C26.1, C27.1, C28.1, C29.1, R25.2, R26.2, R27.2, U5.19 (V+), U6.19 (V+), U7.19 (V+); also elsewhere on the board

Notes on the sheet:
Status LEDs
Displays

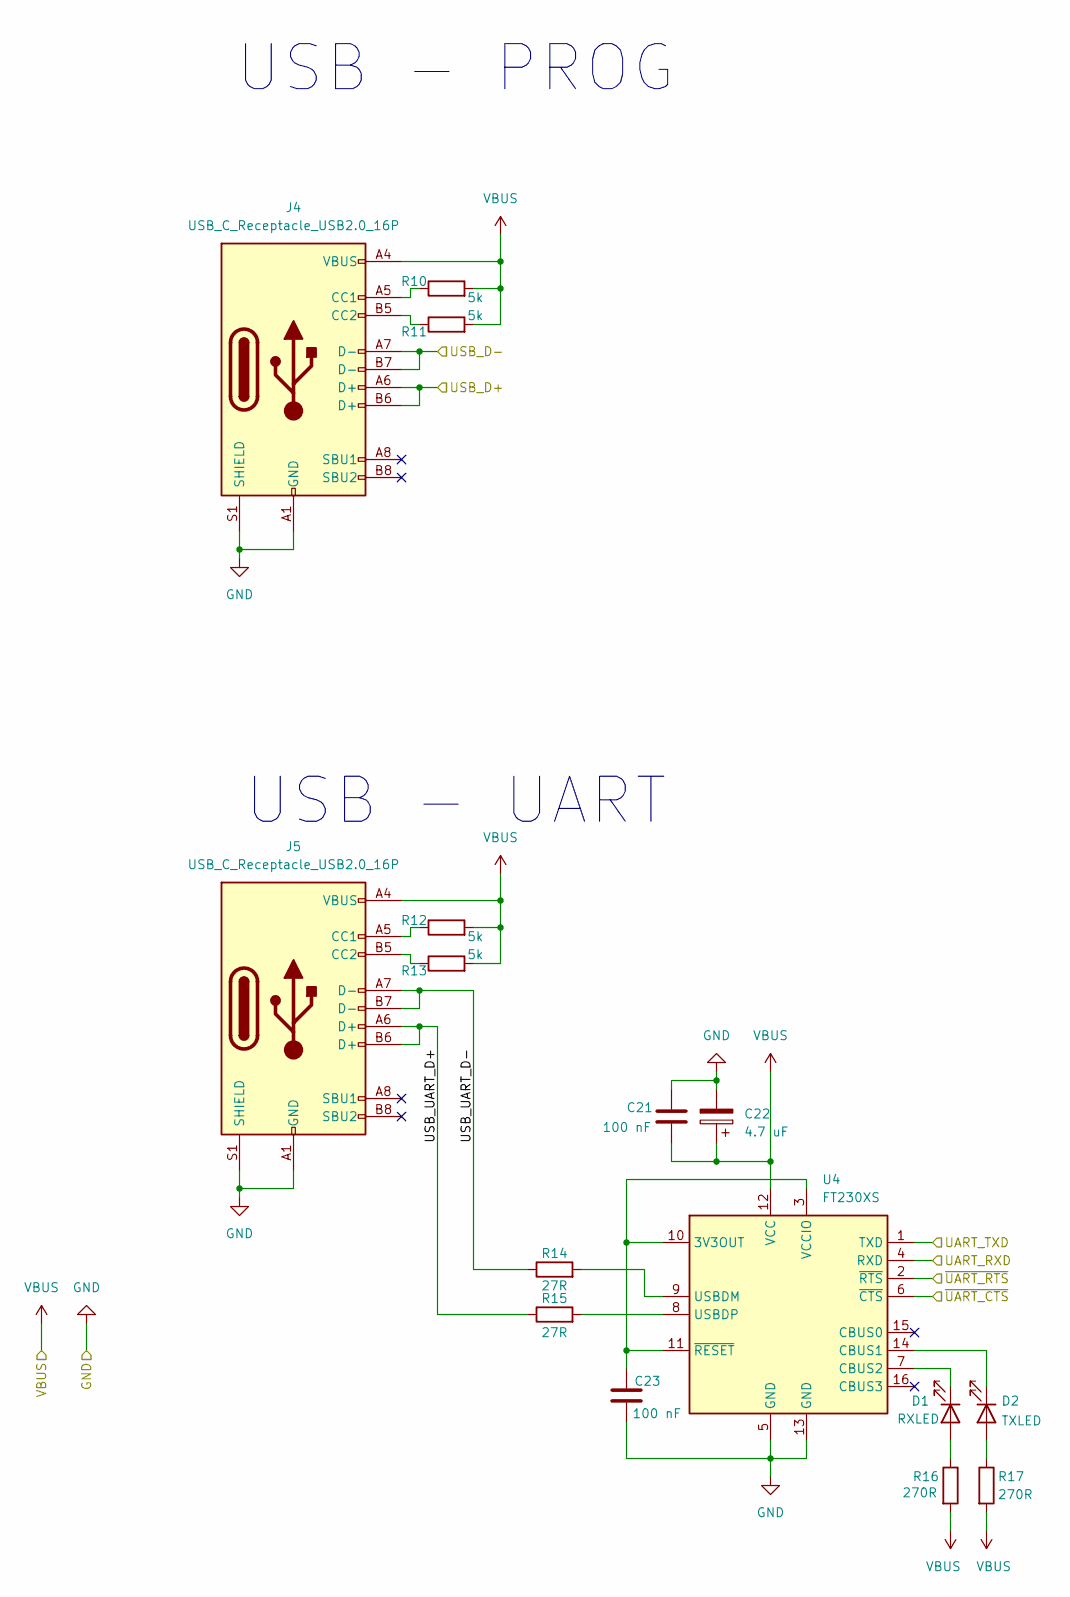
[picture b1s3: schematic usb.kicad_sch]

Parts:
C21, C23: 100 nF; C_0603_1608Metric_Pad1.08x0.95mm_HandSolder
C22: 4.7 uF; CP_Elec_5x4.5
D1: RXLED; LED_0603_1608Metric
D2: TXLED; LED_0603_1608Metric
J4, J5: USB_C_Receptacle_USB2.0_16P; USB_C_Receptacle_GCT_USB4085
R10, R11, R12, R13: 5k; R_0603_1608Metric_Pad0.98x0.95mm_HandSolder
R14, R15: 27R; R_0603_1608Metric_Pad0.98x0.95mm_HandSolder
R16, R17: 270R; R_0603_1608Metric_Pad0.98x0.95mm_HandSolder
U4: FT230XS; SSOP-16_3.9x4.9mm_P0.635mm; LCSC C69082

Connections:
/UART1_CTS: U4.2 (~RTS); also elsewhere on the board
/UART1_RTS: U4.6 (~CTS); also elsewhere on the board
/UART1_RX: U4.1 (TXD); also elsewhere on the board
/UART1_TX: U4.4 (RXD); also elsewhere on the board
/USB D+: J4.A6 (D+), J4.B6 (D+); also elsewhere on the board
/USB D-: J4.A7 (D-), J4.B7 (D-); also elsewhere on the board
/USB/USB_UART_D+: J5.A6 (D+), J5.B6 (D+), R15.1
/USB/USB_UART_D-: J5.A7 (D-), J5.B7 (D-), R14.1
GND: C21.1, C22.2, C23.2, J4.A1 (GND), J4.A12 (GND), J4.B1 (GND), J4.B12 (GND), J4.S1 (SHIELD), J5.A1 (GND), J5.A12 (GND), J5.B1 (GND), J5.B12 (GND), J5.S1 (SHIELD), U4.5 (GND), U4.13 (GND); also elsewhere on the board
unnamed: D1.2 (A), R16.1
unnamed: D1.1 (K), U4.7 (CBUS2)
unnamed: D2.2 (A), R17.1
unnamed: D2.1 (K), U4.14 (CBUS1)
unnamed: J4.A5 (CC1), R10.1
unnamed: J4.B5 (CC2), R11.1
unnamed: J5.A5 (CC1), R12.1
unnamed: J5.B5 (CC2), R13.1
unnamed: C23.1, U4.3 (VCCIO), U4.10 (3V3OUT), U4.11 (~RESET)
unnamed: R14.2, U4.9 (USBDM)
unnamed: R15.2, U4.8 (USBDP)
VBUS: C21.2, C22.1, J4.A4 (VBUS), J4.A9 (VBUS), J4.B4 (VBUS), J4.B9 (VBUS), J5.A4 (VBUS), J5.A9 (VBUS), J5.B4 (VBUS), J5.B9 (VBUS), R10.2, R11.2, R12.2, R13.2, R16.2, R17.2, U4.12 (VCC); also elsewhere on the board

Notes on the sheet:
USB - PROG
USB - UART

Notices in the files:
kicad/kgc.kicad_sch:
See LICENSE file for copyright and license details.
